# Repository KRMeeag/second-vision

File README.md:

# **Second Vision: IoT-Based Smart Glasses for the Visually Impaired**

Real-time object detection and depth estimation on edge hardware, delivering spatial awareness through audio and haptic feedback.

---

## What It Does

Second Vision is a head-mounted assistive device that helps visually impaired users navigate their surroundings:

- **🔊 Audio Feedback** — Announces detected objects with spatial position: *"person left"*, *"car center"*, *"bicycle right"*
- **📳 Haptic Feedback** — Three vibration motors (left, center, right) vibrate proportionally to obstacle proximity
- **🧭 Body- and Head-Height Awareness** — Second Vision watches for the things people walk into: walls, doors, furniture, other people, low branches and overhanging signs at torso and head height. It does not sense the ground, so it will **not** warn about stairs, curbs or drop-offs — every wearer is told this before first use.

Object detection identifies *known* objects (people, cars, obstacles). Depth estimation detects *all* obstacles, including those the AI can't classify. 

---

## Hardware

| Component | Spec |
|---|---|
| Compute | Raspberry Pi 5 (8GB RAM) |
| AI Accelerator | Hailo AI Hat+ (Hailo-8, 26 TOPS) |
| Camera | OV2640 USB Camera Module |
| Motor Controller | ESP32 (wired USB serial) |
| Vibration Motors | 3× ERM (left temple, forehead, right temple) |
| Audio | Bone-conduction earphones |
| Control Panel | Arduino (switches, potentiometers, buttons) |
| Power (motors) | 18650 Li-ion cell via MOSFETs |
| OS | Raspberry Pi OS Trixie (64-bit) |

## Software Stack

| Layer | Technology |
|---|---|
| Detection Model | YOLOv8s (Hailo HEF) |
| Depth Model | SC-DepthV3 (Hailo HEF) |
| Inference Runtime | HailoRT + GStreamer |
| Framework | [`hailo_apps`](https://github.com/hailo-ai/hailo-apps) (pip-installed library) |
| TTS | pyttsx3 / espeak-ng |
| Serial Protocol | Binary (RPi5 ↔ ESP32), Text (Arduino → RPi5) |
| Language | Python 3.13 |

---

## Quick Start

### Prerequisites

- Raspberry Pi 5 with Hailo AI Hat+ installed
- `hailo_apps` package installed in virtual environment
- OV2640 camera connected via USB

### Setup

```bash
# Clone the repository
git clone <repo-url>
cd second-vision-repo

# (FOR RPI ONLY) Make sure to have the necessary PyGOBject and GStreamer bindings (required)
sudo apt install python3-gi python3-gi-cairo gir1.2-gtk-4.0

# Install necessary project dependencies
poetry install 

# Create and activate virtual environment
python3 -m venv --system-site-packages my_hailo_env
source my_hailo_env/bin/activate
```

### Run

```bash
# Mock mode (no hardware needed — for development)
./scripts/run.sh --mock

# With camera (display mode for testing)
./scripts/run.sh --input rawusb:///dev/video0 --width 640 --height 360 --frame-rate 25

# Full system (headless, with ESP32 and Arduino)
./scripts/run.sh --input rawusb:///dev/video0 --width 640 --height 360 --frame-rate 25 \
    --serial-port /dev/ttyUSB0 \
    --config-port /dev/ttyACM0 \
    --headless
```

---

## Architecture

```
Camera → Hailo-8 NPU ─┬─→ YOLOv8s (detection) → TTS → Speaker
                       └─→ SC-DepthV3 (depth)  → ESP32 → 3× Motors

Arduino Control Panel → RPi5 → Runtime configuration
```

The system runs a GStreamer pipeline with two parallel inference branches. Each branch has a callback that pushes results into a thread-safe queue. Daemon worker threads consume from the queues and produce outputs (audio, serial commands).

See [`documentation/ARCHITECTURE.md`](documentation/ARCHITECTURE.md) for the full architecture document.

---

## Project Structure

```
second-vision-repo/
├── src/
│   └── second_vision/
│       ├── main.py                ← Entry point
│       ├── pipeline/              ← GStreamer pipeline + callbacks
│       ├── workers/               ← TTS, serial, config reader threads
│       ├── core/                  ← Config, protocol, depth utilities
│       └── mock/                  ← Fake data generators for --mock mode
├── scripts/
│   └── run.sh                     ← Launch script
├── config/                        ← Default settings
├── tests/                         ← Unit tests
├── documentation/                       ← Documentation
│   ├── PROJECT.md                 ← Project overview
│   ├── ARCHITECTURE.md            ← System architecture
│   ├── DECISIONS.md               ← Architectural decisions log
│   ├── PLAN.md                    ← Implementation phases
│   └── TASKS.md                   ← Task breakdown
├── CLAUDE.md                      ← AI agent instructions
└── README.md                      ← You are here

```

---

## Development

### Mock Mode

Run the full system without any hardware. Generates fake detections and depth data for testing workers:

```bash
./scripts/run.sh --mock
```

### Stub Pattern

Every component starts as a working stub. Replace the private functions marked `# STUBS BELOW` with real implementations. The worker loop, queue interface, and config integration never change.

See [`documentation/PLAN.md`](documentation/PLAN.md) for the phased implementation plan.

### Running Tests

```bash
source my_hailo_env/bin/activate
python3 -m pytest tests/
```

---

## Documentation

| Document | Description |
|---|---|
| [`AGENT.md`](AGENT.md) | Instructions for AI coding agents — read this first |
| [`PROJECT.md`](documentation/PROJECT.md) | Project overview, team, hardware specs |
| [`ARCHITECTURE.md`](documentation/ARCHITECTURE.md) | System architecture, data flow, protocols |
| [`DECISIONS.md`](documentation/DECISIONS.md) | All architectural decisions with rationale |
| [`PLAN.md`](documentation/PLAN.md) | 10-phase implementation plan |
| [`TASKS.md`](documentation/TASKS.md) | Granular task checklist |

---

## Researchers

- **Kenzhu Aguilera**
- **Waldric Jude S. Garcia**
- **Kenth Razen M. Magbanua**
- **Reiven O. Jasa**

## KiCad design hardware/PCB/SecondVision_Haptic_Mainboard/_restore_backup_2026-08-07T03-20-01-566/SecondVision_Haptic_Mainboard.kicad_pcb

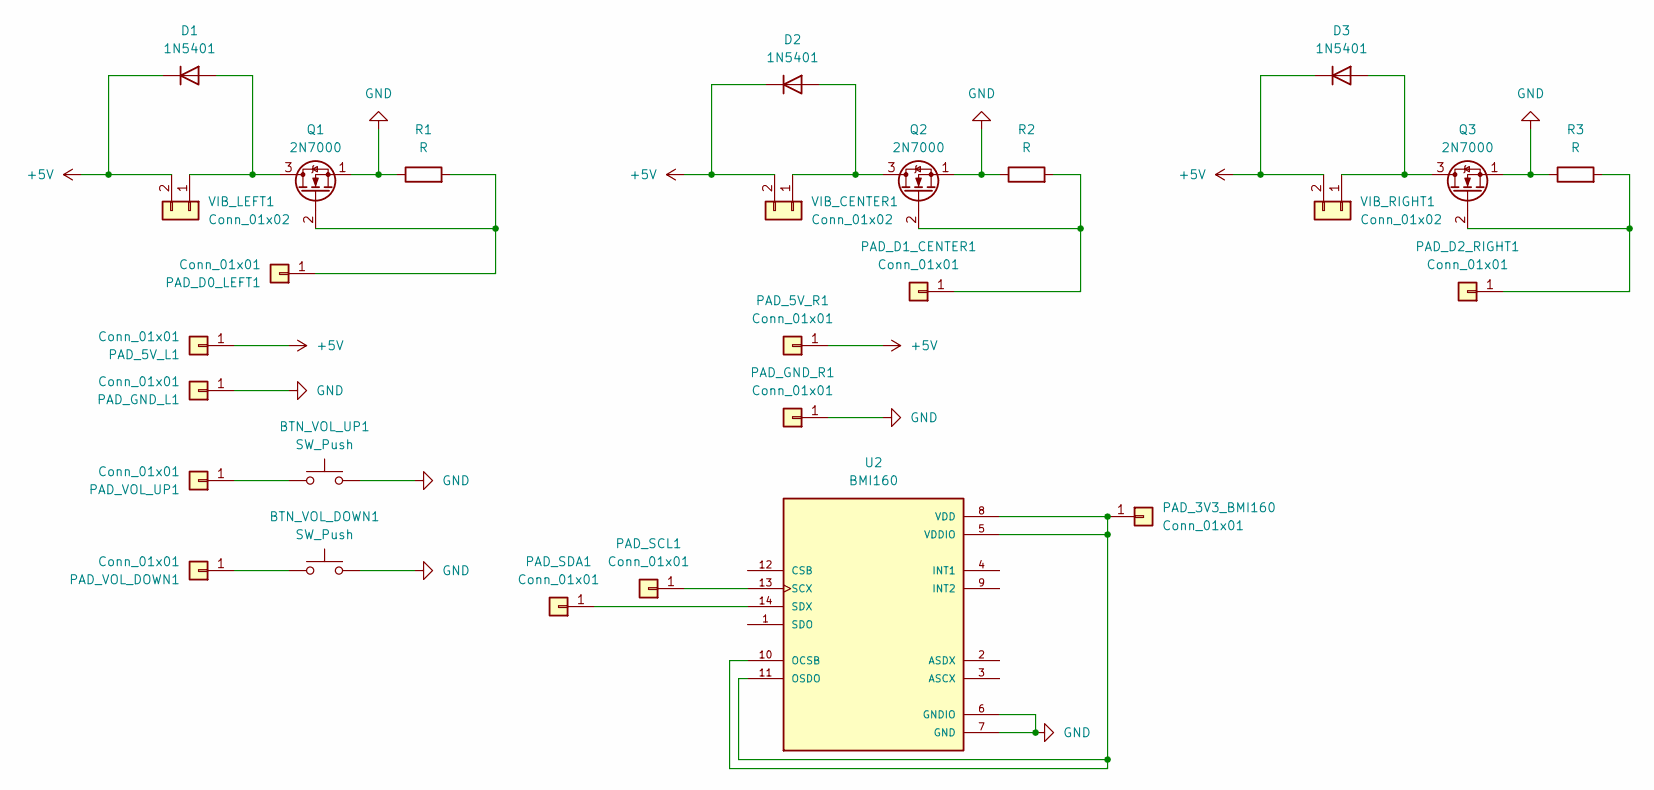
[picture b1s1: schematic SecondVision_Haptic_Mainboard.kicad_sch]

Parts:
BTN_VOL_DOWN1: SW_Push; SW_SPST_B3U-1000P
BTN_VOL_UP1: SW_Push; SW_SPST_B3U-1000P
D1, D2, D3: 1N5401; D_SOD-123
PAD_3V3_BMI160, PAD_5V_L1, PAD_5V_R1: Conn_01x01; PinHeader_1x01_P2.54mm_Vertical
PAD_D0_LEFT1, PAD_D1_CENTER1, PAD_D2_RIGHT1: Conn_01x01; PinHeader_1x01_P2.54mm_Vertical
PAD_GND_L1: Conn_01x01; PinHeader_1x01_P2.54mm_Vertical
PAD_GND_R1: Conn_01x01; PinHeader_1x01_P2.54mm_Vertical
PAD_SCL1: Conn_01x01; PinHeader_1x01_P2.54mm_Vertical
PAD_SDA1: Conn_01x01; PinHeader_1x01_P2.54mm_Vertical
PAD_VOL_DOWN1: Conn_01x01; PinHeader_1x01_P2.54mm_Vertical
PAD_VOL_UP1: Conn_01x01; PinHeader_1x01_P2.54mm_Vertical
Q1, Q2, Q3: 2N7000; SOT-23
R1, R2, R3: R; R_0603_1608Metric
U2: BMI160; PQFN50P250X300X88-14N; PARTREV 1.0
VIB_CENTER1: Conn_01x02; PinHeader_1x02_P2.54mm_Vertical
VIB_LEFT1: Conn_01x02; PinHeader_1x02_P2.54mm_Vertical
VIB_RIGHT1: Conn_01x02; PinHeader_1x02_P2.54mm_Vertical

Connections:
+5V: D1.1 (K), D2.1 (K), D3.1 (K), PAD_5V_L1.1 (Pin_1_1), PAD_5V_R1.1 (Pin_1_1), VIB_CENTER1.2, VIB_LEFT1.2, VIB_RIGHT1.2
GND: BTN_VOL_DOWN1.2, BTN_VOL_UP1.2, PAD_GND_L1.1 (Pin_1_1), PAD_GND_R1.1 (Pin_1_1), Q1.1 (S), Q2.1 (S), Q3.1 (S), R1.1, R2.1, R3.1, U2.6 (GNDIO), U2.7 (GND)
unnamed: D1.2 (A), Q1.3 (D), VIB_LEFT1.1
unnamed: D2.2 (A), Q2.3 (D), VIB_CENTER1.1
unnamed: D3.2 (A), Q3.3 (D), VIB_RIGHT1.1
unnamed: PAD_3V3_BMI160.1 (Pin_1_1), U2.5 (VDDIO), U2.8 (VDD), U2.10 (OCSB), U2.11 (OSDO)
unnamed: PAD_D0_LEFT1.1 (Pin_1_1), Q1.2 (G), R1.2
unnamed: PAD_D1_CENTER1.1 (Pin_1_1), Q2.2 (G), R2.2
unnamed: PAD_D2_RIGHT1.1 (Pin_1_1), Q3.2 (G), R3.2
unnamed: PAD_SCL1.1 (Pin_1_1), U2.13 (SCX)
unnamed: PAD_SDA1.1 (Pin_1_1), U2.14 (SDX)
unnamed: BTN_VOL_DOWN1.1, PAD_VOL_DOWN1.1 (Pin_1_1)
unnamed: BTN_VOL_UP1.1, PAD_VOL_UP1.1 (Pin_1_1)

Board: 2 copper layers, 27 parts (0 on the bottom side), 13 nets, no tracks yet.

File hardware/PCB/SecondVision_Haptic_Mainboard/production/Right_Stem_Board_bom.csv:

Designator,Footprint,Quantity,Value,LCSC Part #
"D2, D3",D_SOD-123,2,1N5401,
"PAD_5V_R1, PAD_D1_CENTER1, PAD_D2_RIGHT1, PAD_GND_R1",PinHeader_1x01_P2.54mm_Vertical,4,Conn_01x01,
"Q2, Q3",SOT-23,2,2N7000,
"R2, R3",0603,2,R,
"VIB_CENTER1, VIB_RIGHT1",PinHeader_1x02_P2.54mm_Vertical,2,Conn_01x02,

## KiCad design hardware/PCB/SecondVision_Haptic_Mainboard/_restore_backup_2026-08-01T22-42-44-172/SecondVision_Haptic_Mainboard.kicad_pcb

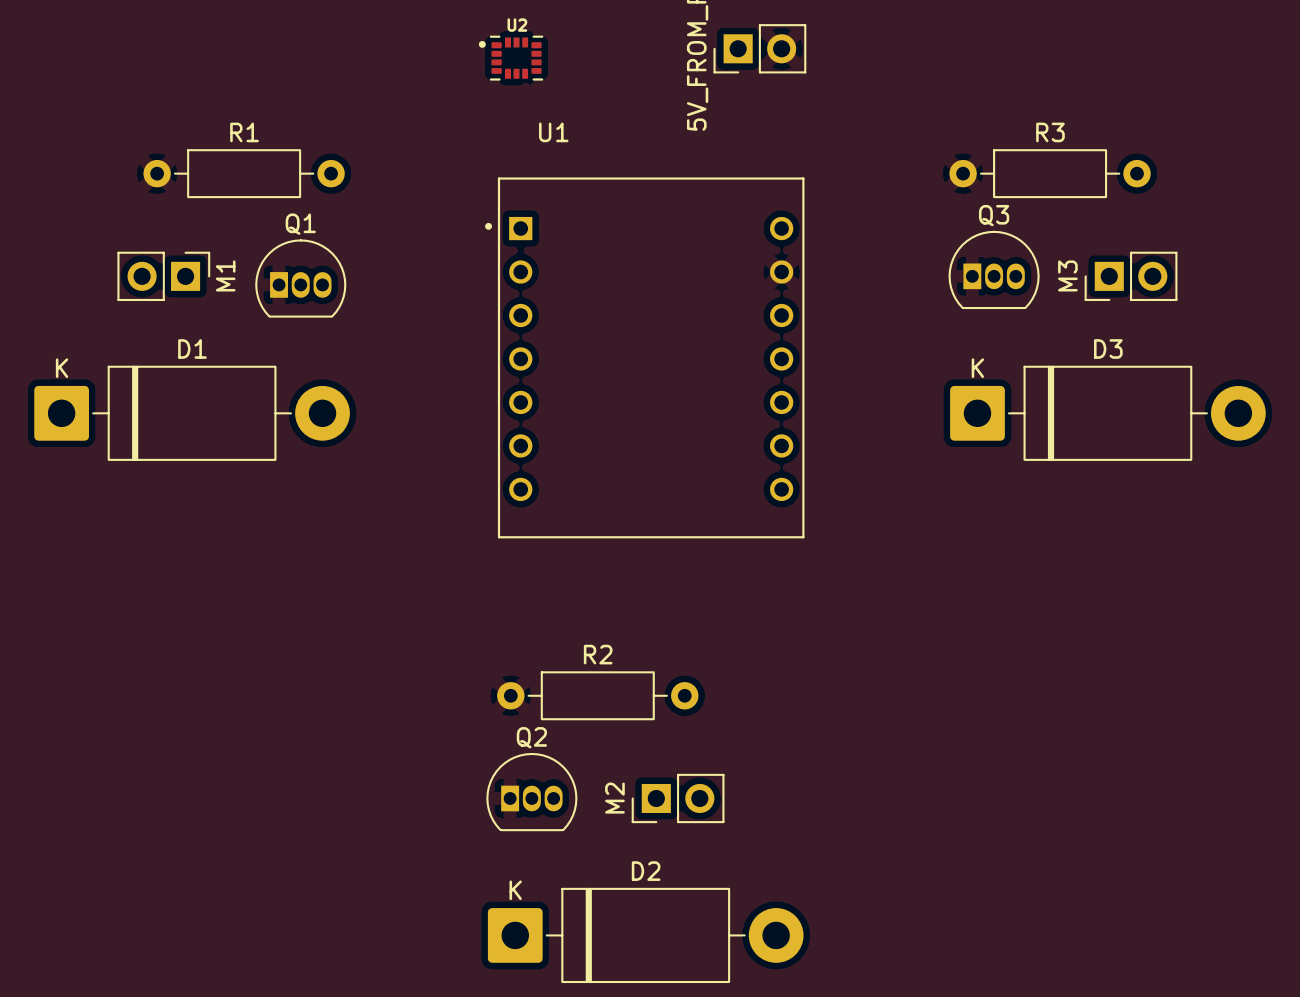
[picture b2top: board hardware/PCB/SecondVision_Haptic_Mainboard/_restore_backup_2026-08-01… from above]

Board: 2 copper layers, 15 parts (0 on the bottom side), 11 nets, no tracks yet.

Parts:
5V_FROM_PI1: Conn_01x02; PinHeader_1x02_P2.54mm_Vertical
D1, D2, D3: 1N5401; D_DO-201AD_P15.24mm_Horizontal
M1, M2, M3: Motor_DC; PinHeader_1x02_P2.54mm_Vertical
Q1, Q2, Q3: 2N7000; TO-92_Inline
R1, R2, R3: R; R_Axial_DIN0207_L6.3mm_D2.5mm_P10.16mm_Horizontal
U1: XIAO_ESP32C3; MODULE_XIAO_ESP32C3
U2: BMI160; PQFN50P250X300X88-14N

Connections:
+3.3V: U1.12 (VCC_3V3), U2.8 (VDD)
+5V: 5V_FROM_PI1.1, D1.1 (K), D2.1 (K), D3.1 (K), M1.1 (+), M2.1 (+), M3.1 (+), U1.14 (VUSB)
GND: 5V_FROM_PI1.2, Q1.1 (S), Q2.1 (S), Q3.1 (S), R1.1, R2.1, R3.1, U1.13 (GND), U2.7 (GND)
unnamed: D1.2 (A), M1.2 (-), Q1.3 (D)
unnamed: D2.2 (A), M2.2 (-), Q2.3 (D)
unnamed: D3.2 (A), M3.2 (-), Q3.3 (D)
unnamed: Q1.2 (G), R1.2, U1.1 (D0)
unnamed: Q2.2 (G), R2.2, U1.2 (D1)
unnamed: Q3.2 (G), R3.2, U1.3 (D2)
unnamed: U1.5 (D4), U2.14 (SDX)
unnamed: U1.6 (D5), U2.13 (SCX)

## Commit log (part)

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2026-06-29 feat: configure initial draft of vision pipelines
2026-06-29 feat: create new version of sv pipeline that includes wrapper for Obj Detect
2026-06-29 feat: add test callback functions for both depth and obj detection
2026-06-30 feat: add script to easily run v2 pipeline
2026-06-30 feat: add script to easily run v3 pipeline
2026-06-30 feat: add script to easily run v3 pipeline with callback functions
